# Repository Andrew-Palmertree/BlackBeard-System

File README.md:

# Blackbeard-System
This code is for our secure package delivery system, The Blackbeard System. This code will include object and facial recognition along with code for our servo control.

The idea behind Blackbeard is that it will allow delivered packages to end up securely inside of your home versus being left on your porch or inside some clunky metal box. The BlackBeard system incorporates a front door with a package drop located in the lower half of the door, which will drop the package in front of the front door inside of the home. It can fit packages equal to or smaller than 18x20. A camera with the system will be used to detect delivery drivers using artificial intelligence. Upon detection, the chute will open automatically for the delivery driver. The delivery man can put your package inside, then it will sense when no more packages are being delivered and automatically close, dropping the packages inside of the Blackbeard owner’s home. 
This product has space in quite a large market, to be installed on existing homes by DIYers or professional installation by contractors, or with over 1.8 million houses being built a year. This can also be installed on homes being newly built. As a company we will offer basic dimensions and different door materials, or interested customers can request custom dimensions to match their home.
The biggest areas of focus on this project are being able to depict delivery drivers using object recognition and interfacing the servo motors that control the package slip at the bottom of the front door. 
Time permitting, we would also like to implement a type of keyless entry into the home. This method would involve facial recognition of residents (utilizing the same camera for package deliveries) and/or a wireless entry system that unlocks the door when a keyfob is within proximity of the door (similar to keyless entry on modern automobiles). Despite our desire to add this additional feature, the main focus of the project is to get the package delivery system fully functional before pursuing any additional features. 

The goal of our proof of concept is to get the backend code fully functional with the servo motors, camera, & motion sensor interfaced properly with the Raspberry Pi. We plan to use a Raspberry Pi 3b+ for demonstration purposes, and it is likely we will fabricate our own PCB with a microcontroller when it comes time to create our prototype. We plan to implement computer vision with the camera and Raspberry Pi to begin training our system to detect delivery drivers and to recognize different faces. The system will be programmed using either Python or C++ depending on the route we choose to take in terms of an object recognition library. The primary goal is to get the package delivery system functional first, and time permitting we will pursue our secondary goal of creating a functional keyless entry system into the home. Below is a shortened, itemized list of what we want to be able to accomplish in our proof of concept. More detail into the major components is covered later on in this section. It is worth noting that we plan on testing all the components individually.
- Successfully interface components with Raspberry Pi
- Train a neural network to recognize delivery drivers with packages
- Camera is able to transmit real-time images to the Raspberry Pi
- Be able to trigger opening/closing of the package chute upon detection of a delivery driver
- Motion sensor is able to successfully detect motion inside the package chute
- After a period of time with no new motion detected, the chute will close

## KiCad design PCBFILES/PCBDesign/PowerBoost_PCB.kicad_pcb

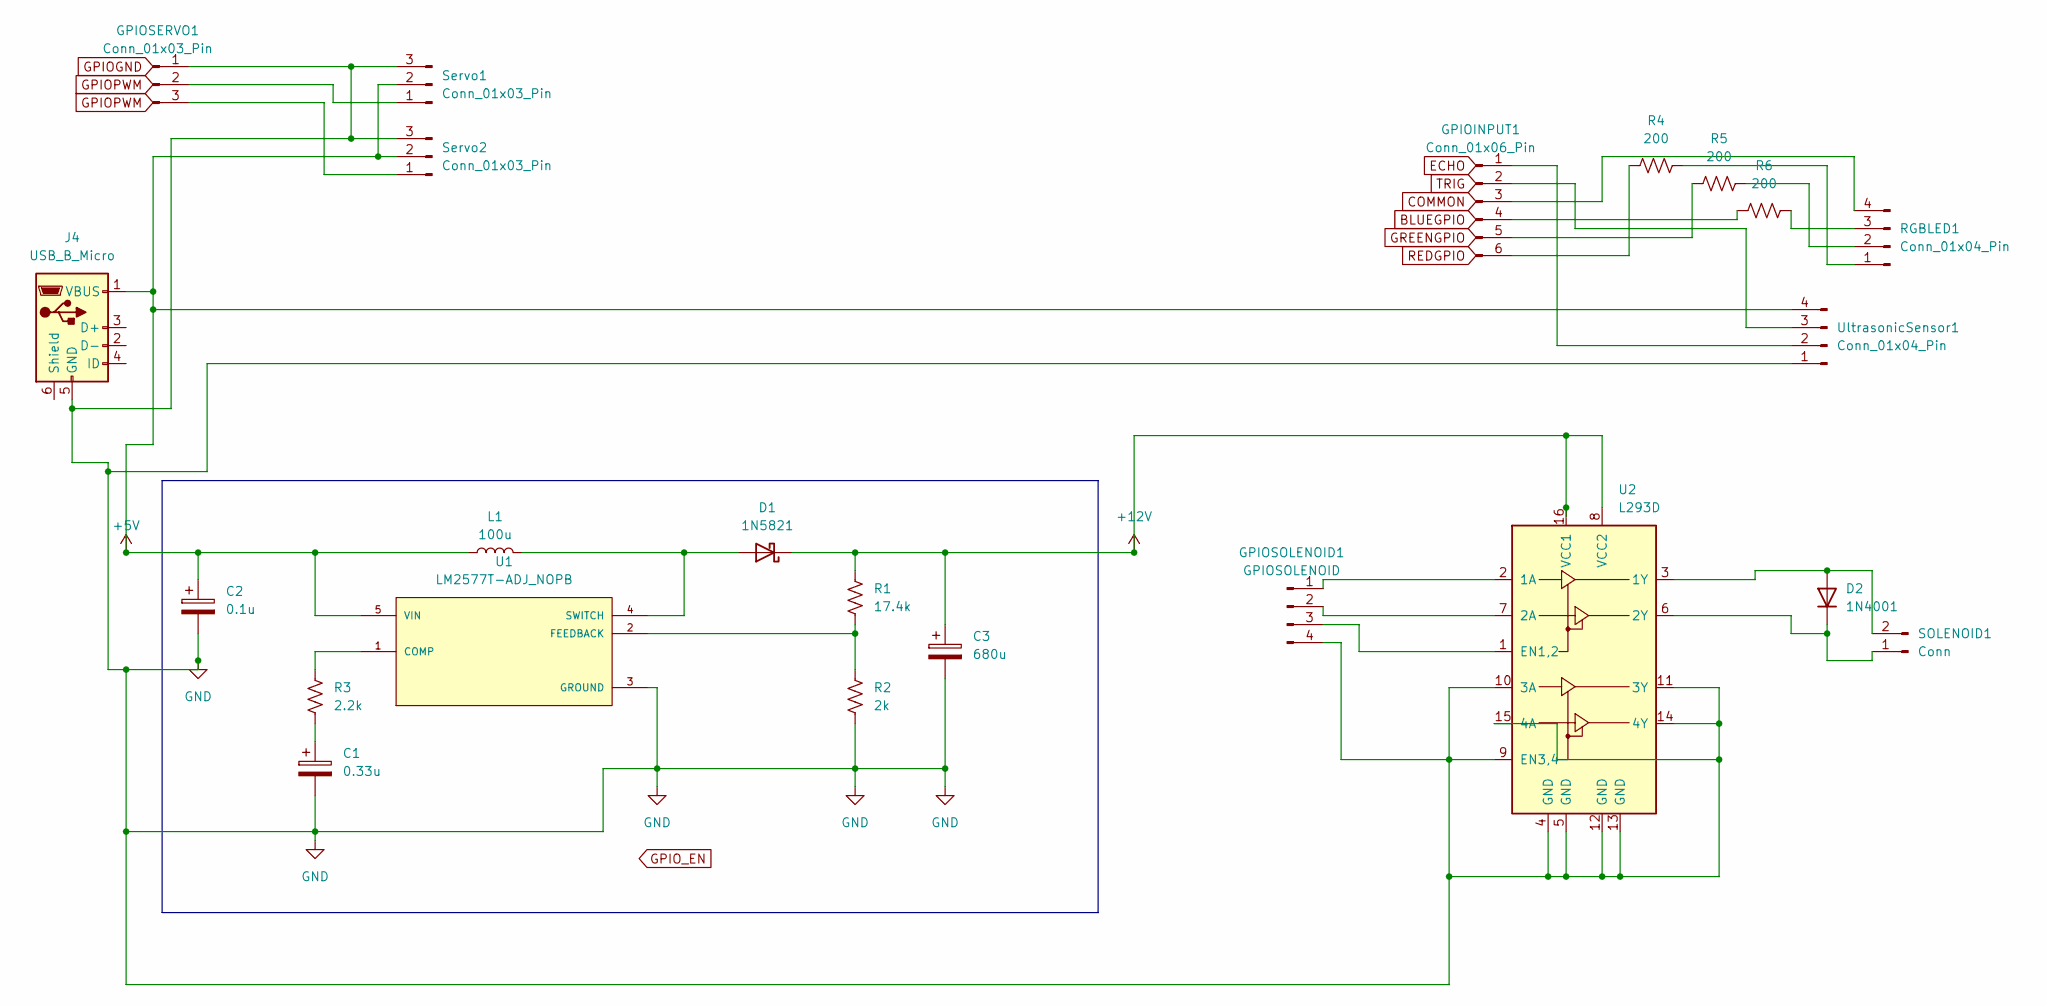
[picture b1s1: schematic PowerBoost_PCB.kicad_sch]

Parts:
C1: 0.33u; CP_Radial_D5.0mm_P2.50mm
C2: 0.1u; CP_Radial_D5.0mm_P2.50mm
C3: 680u; CP_Radial_D10.0mm_P5.00mm
D1: 1N5821; D_DO-201AD_P15.24mm_Horizontal
D2: 1N4001; D_DO-41_SOD81_P10.16mm_Horizontal
GPIOINPUT1: Conn_01x06_Pin
GPIOSERVO1: Conn_01x03_Pin
GPIOSOLENOID1: GPIOSOLENOID; JST_EH_B4B-EH-A_1x04_P2.50mm_Vertical
J4: USB_B_Micro
L1: 100u; L_Radial_D8.7mm_P5.00mm_Fastron_07HCP
R1: 17.4k; R_Axial_DIN0204_L3.6mm_D1.6mm_P7.62mm_Horizontal
R2: 2k; R_Axial_DIN0204_L3.6mm_D1.6mm_P7.62mm_Horizontal
R3: 2.2k; R_Axial_DIN0204_L3.6mm_D1.6mm_P7.62mm_Horizontal
R4, R5, R6: 200; R_Axial_DIN0204_L3.6mm_D1.6mm_P7.62mm_Horizontal
RGBLED1: Conn_01x04_Pin
SOLENOID1: Conn; JST_EH_B2B-EH-A_1x02_P2.50mm_Vertical
Servo1, Servo2: Conn_01x03_Pin
U1: LM2577T-ADJ_NOPB; VREG_LM2577T-ADJ_NOPB; PARTREV D
U2: L293D; DIP-16_W7.62mm
UltrasonicSensor1: Conn_01x04_Pin

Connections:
+5V: C2.1, J4.1 (VBUS), L1.1, Servo1.2, Servo2.2, U1.5 (VIN), UltrasonicSensor1.4
+12V: C3.1, D1.1 (K), R1.1, U2.8 (VCC2), U2.16 (VCC1)
GND: C1.2, C2.2, C3.2, GPIOSERVO1.1, GPIOSOLENOID1.4, J4.5 (GND), R2.2, Servo1.3, Servo2.3, U1.3 (GROUND), U2.4 (GND), U2.5 (GND), U2.9 (EN3,4), U2.10 (3A), U2.11 (3Y), U2.12 (GND), U2.13 (GND), U2.14 (4Y), U2.15 (4A), UltrasonicSensor1.1
unnamed: C1.1, R3.2
unnamed: D1.2 (A), L1.2, U1.4 (SWITCH)
unnamed: D2.2 (A), SOLENOID1.2, U2.3 (1Y)
unnamed: D2.1 (K), SOLENOID1.1, U2.6 (2Y)
unnamed: GPIOINPUT1.1, UltrasonicSensor1.2
unnamed: GPIOINPUT1.2, UltrasonicSensor1.3
unnamed: GPIOINPUT1.3, RGBLED1.4
unnamed: GPIOINPUT1.4, R6.1
unnamed: GPIOINPUT1.5, R5.2
unnamed: GPIOINPUT1.6, R4.1
unnamed: GPIOSERVO1.2, Servo1.1
unnamed: GPIOSERVO1.3, Servo2.1
unnamed: GPIOSOLENOID1.1, U2.2 (1A)
unnamed: GPIOSOLENOID1.2, U2.7 (2A)
unnamed: GPIOSOLENOID1.3, U2.1 (EN1,2)
unnamed: R4.2, RGBLED1.1
unnamed: R5.1, RGBLED1.2
unnamed: R6.2, RGBLED1.3
unnamed: R3.1, U1.1 (COMP)
unnamed: R1.2, R2.1, U1.2 (FEEDBACK)

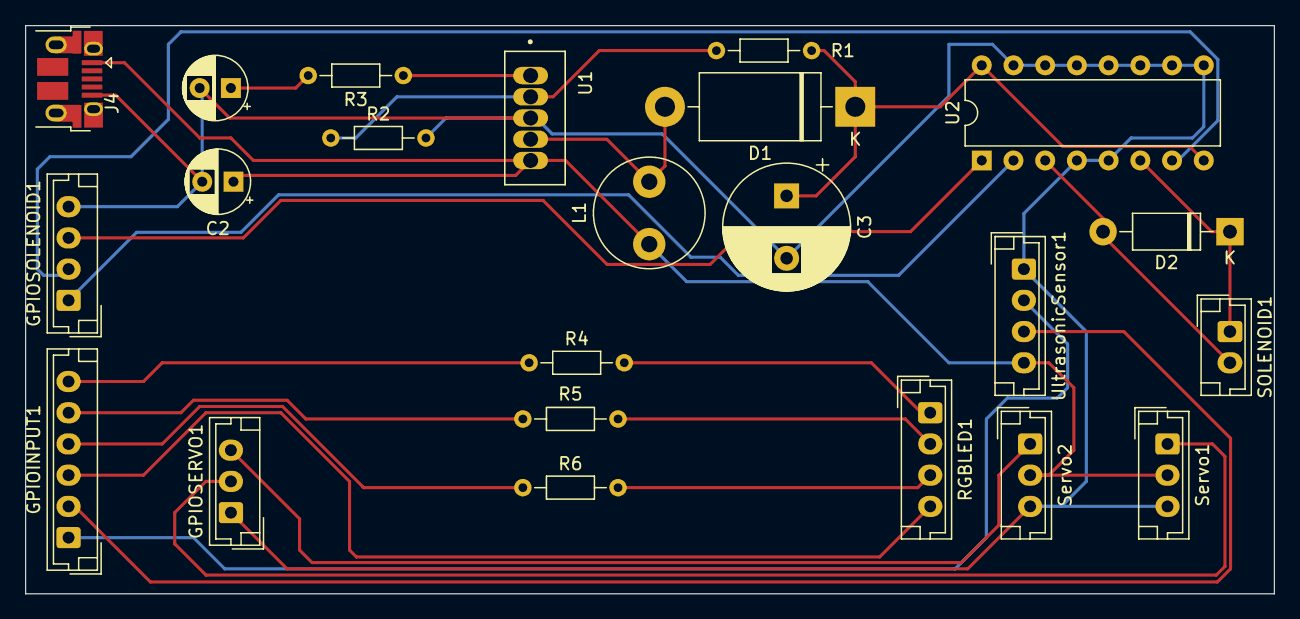
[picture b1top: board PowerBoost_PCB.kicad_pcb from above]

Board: 2 copper layers, 100.0 x 45.5 mm, 23 parts (0 on the bottom side), 23 nets.

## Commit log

2023-10-19 Update README.md
    Added the information of our proof of concept and general idea of the project
2023-10-20 FPS Code(if needed)
    This is the code used to create the separate threading for the camera. PiCameraFPS is a test file to run, this will show how the multi threading process can improve our systems performance
2023-10-26 PiVideoStream.py to FPS.py
2023-10-26 Create thread_demo.py(This will run FPS and WebStream to show results
2023-10-26 Add files via upload
    UPDATES from servocontro.py - more organized code
2023-10-31 Add files via upload
    Added a new file to show how I installed Opencv, Keras, and Tensorflow onto the raspberry pi. Enjoy! :)
2023-10-31 Update Virtual_Environment_Setup.md
    fix the images not showing up
2023-12-01 Add files via upload
    Up to date versions of main & GPIO functions as of 11/30/2023
2024-03-27 Add PCBFILES to repository
2024-03-27 PCB Design Files
2024-03-27 PCB Manufature
2024-03-27 Putting RPI files in one directory
2024-04-09 Update Proto_GPIOZERO_Functions.py
    updated sleep functions
2024-04-10 Add files via upload
    threaded files
2024-04-15 MOST UP TO DATE AND HOPEFULLY FINAL VERSION
2024-05-01 Add files via upload
    added object recognition code
2024-05-01 Add files via upload
    added server code
2024-05-01 Add files via upload
    added face folders
2024-05-01 Add files via upload
    added unknown
2024-05-01 Add files via upload
    added scott's images
2024-05-01 Add files via upload
    Added Justin's photos
2024-05-01 Add files via upload
    Added Andrew's image
2024-05-01 Add files via upload
    Added images for Parbin
2024-05-01 Add files via upload
    Imanol
2024-05-01 Add files via upload
    Will
2024-05-01 Add files via upload
    Parbin
2024-05-01 Added files of training face recognition
